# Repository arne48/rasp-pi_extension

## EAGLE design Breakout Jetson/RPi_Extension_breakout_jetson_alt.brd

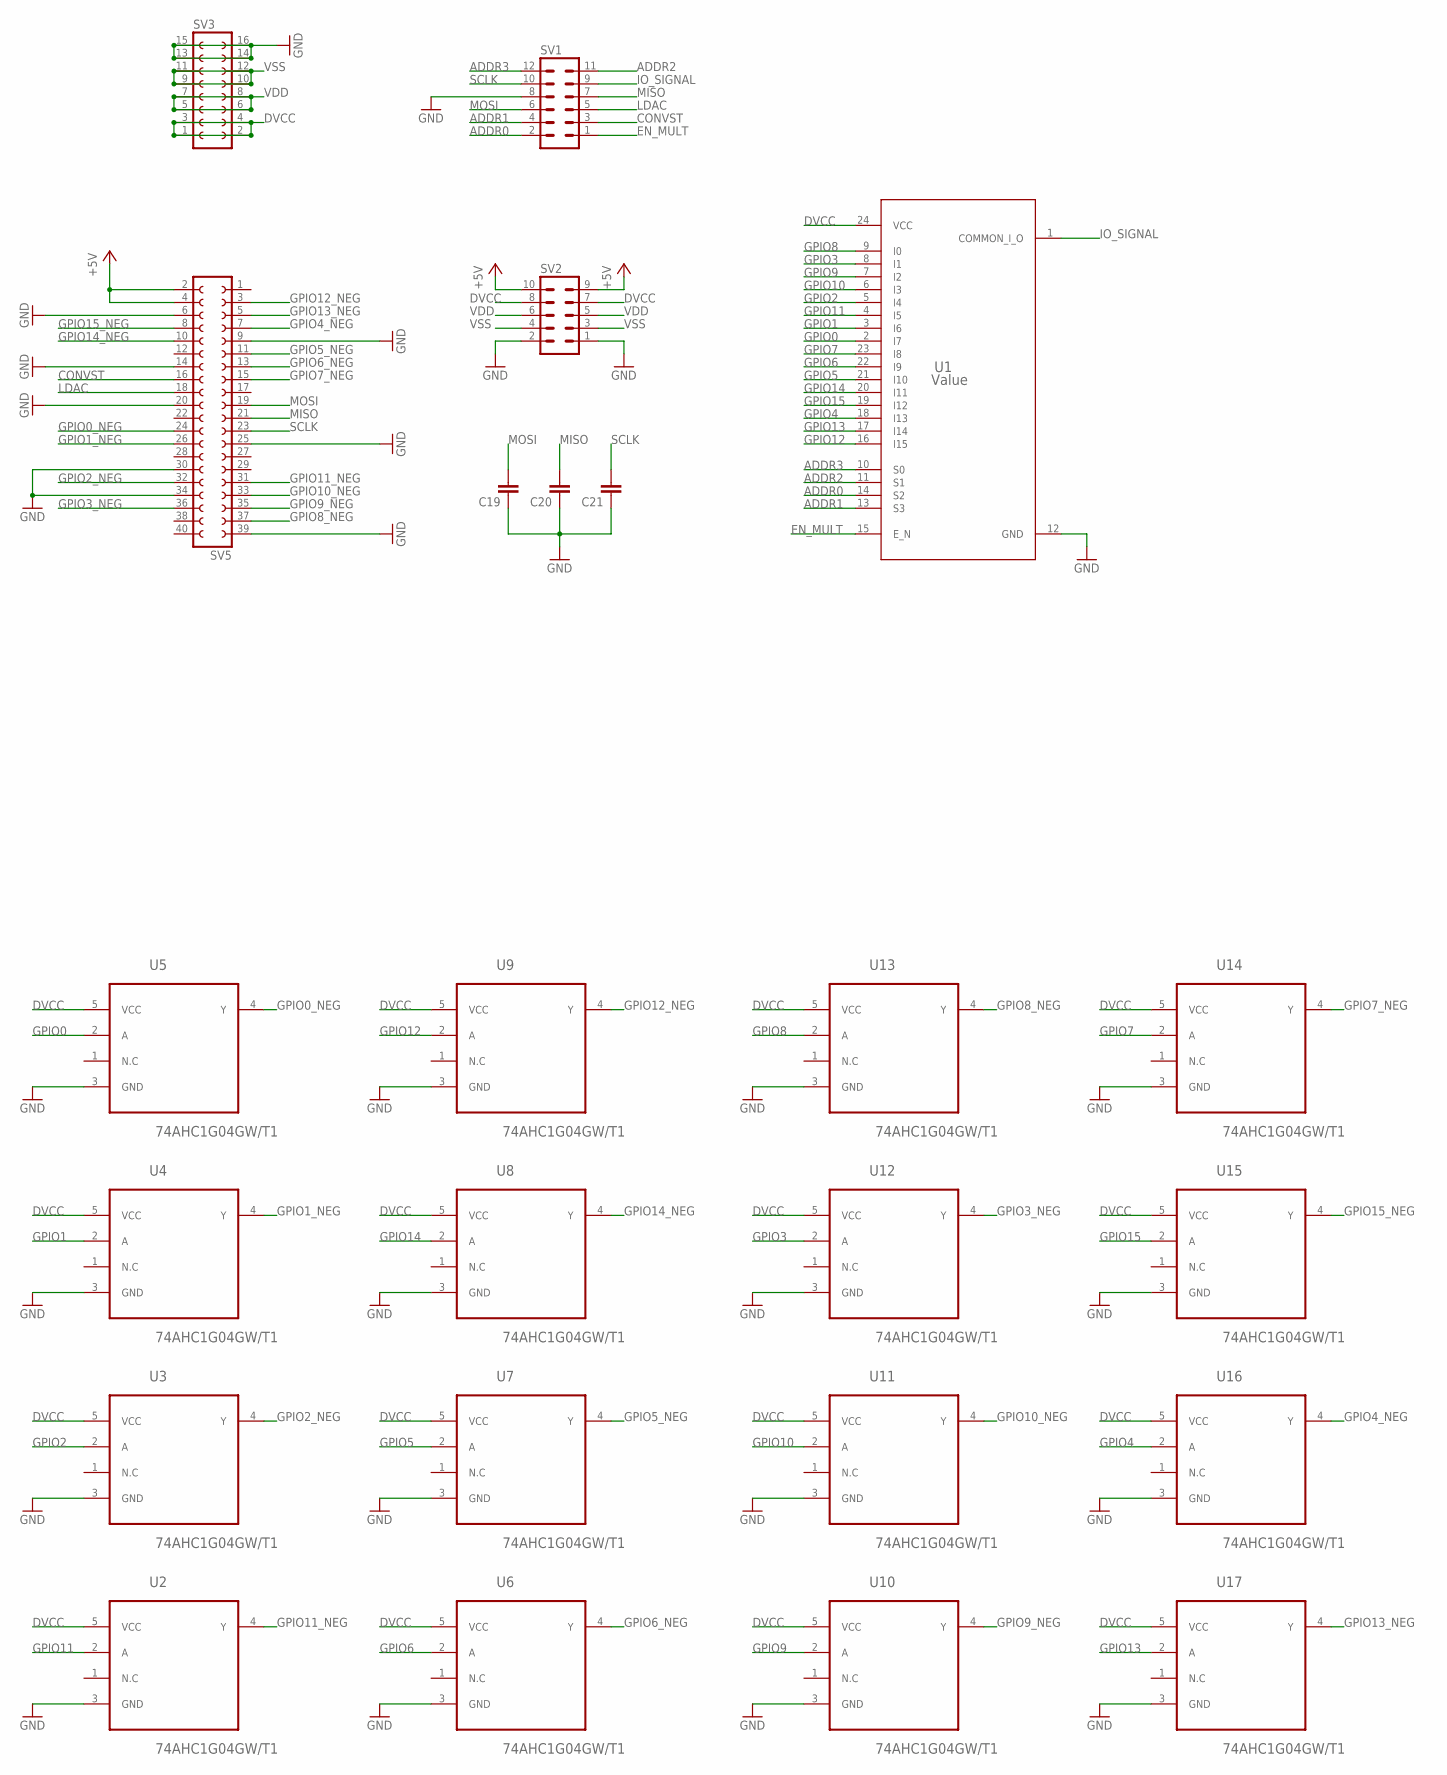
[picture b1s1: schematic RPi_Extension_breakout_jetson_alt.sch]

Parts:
C19, C20, C21: C-EUC0603; C0603
SV1: MA06-2
SV2: MA05-2
SV3: FE08-2
SV5: FE20-2
U1: Value; DB0024A_N
U2, U3, U4, U5, U6, U7, U8, U9, U10, U11, U12, U13, U14, U15, U16, U17: 74AHC1G04GW/T1; SOT65P210X110-5N

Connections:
+5V: SV2.9, SV2.10, SV5.2, SV5.4
ADDR0: SV1.2, U1.14 (S2)
ADDR1: SV1.4, U1.13 (S3)
ADDR2: SV1.11, U1.11 (S1)
ADDR3: SV1.12, U1.10 (S0)
CONVST: SV1.3, SV5.16
DVCC: SV2.7, SV2.8, SV3.1, SV3.2, SV3.3, SV3.4, U1.24 (VCC), U2.5 (VCC), U3.5 (VCC), U4.5 (VCC), U5.5 (VCC), U6.5 (VCC), U7.5 (VCC), U8.5 (VCC), U9.5 (VCC), U10.5 (VCC), U11.5 (VCC), U12.5 (VCC), U13.5 (VCC), U14.5 (VCC), U15.5 (VCC), U16.5 (VCC), U17.5 (VCC)
EN_MULT: SV1.1, U1.15 (E_N)
GND: C19.1, C20.1, C21.1, SV1.8, SV2.1, SV2.2, SV3.13, SV3.14, SV3.15, SV3.16, SV5.6, SV5.9, SV5.14, SV5.20, SV5.25, SV5.30, SV5.34, SV5.39, U1.12 (GND), U2.3 (GND), U3.3 (GND), U4.3 (GND), U5.3 (GND), U6.3 (GND), U7.3 (GND), U8.3 (GND), U9.3 (GND), U10.3 (GND), U11.3 (GND), U12.3 (GND), U13.3 (GND), U14.3 (GND), U15.3 (GND), U16.3 (GND), U17.3 (GND)
GPIO0: U1.2 (I7), U5.2 (A)
GPIO0_NEG: SV5.24, U5.4 (Y)
GPIO1: U1.3 (I6), U4.2 (A)
GPIO1_NEG: SV5.26, U4.4 (Y)
GPIO2: U1.5 (I4), U3.2 (A)
GPIO2_NEG: SV5.32, U3.4 (Y)
GPIO3: U1.8 (I1), U12.2 (A)
GPIO3_NEG: SV5.36, U12.4 (Y)
GPIO4: U1.18 (I13), U16.2 (A)
GPIO4_NEG: SV5.7, U16.4 (Y)
GPIO5: U1.21 (I10), U7.2 (A)
GPIO5_NEG: SV5.11, U7.4 (Y)
GPIO6: U1.22 (I9), U6.2 (A)
GPIO6_NEG: SV5.13, U6.4 (Y)
GPIO7: U1.23 (I8), U14.2 (A)
GPIO7_NEG: SV5.15, U14.4 (Y)
GPIO8: U1.9 (I0), U13.2 (A)
GPIO8_NEG: SV5.37, U13.4 (Y)
GPIO9: U1.7 (I2), U10.2 (A)
GPIO9_NEG: SV5.35, U10.4 (Y)
GPIO10: U1.6 (I3), U11.2 (A)
GPIO10_NEG: SV5.33, U11.4 (Y)
GPIO11: U1.4 (I5), U2.2 (A)
GPIO11_NEG: SV5.31, U2.4 (Y)
GPIO12: U1.16 (I15), U9.2 (A)
GPIO12_NEG: SV5.3, U9.4 (Y)
GPIO13: U1.17 (I14), U17.2 (A)
GPIO13_NEG: SV5.5, U17.4 (Y)
GPIO14: U1.20 (I11), U8.2 (A)
GPIO14_NEG: SV5.10, U8.4 (Y)
GPIO15: U1.19 (I12), U15.2 (A)
GPIO15_NEG: SV5.8, U15.4 (Y)
IO_SIGNAL: SV1.9, U1.1 (COMMON_I_O)
LDAC: SV1.5, SV5.18
MISO: C20.2, SV1.7, SV5.21
MOSI: C19.2, SV1.6, SV5.19
SCLK: C21.2, SV1.10, SV5.23
VDD: SV2.5, SV2.6, SV3.5, SV3.6, SV3.7, SV3.8
VSS: SV2.3, SV2.4, SV3.9, SV3.10, SV3.11, SV3.12

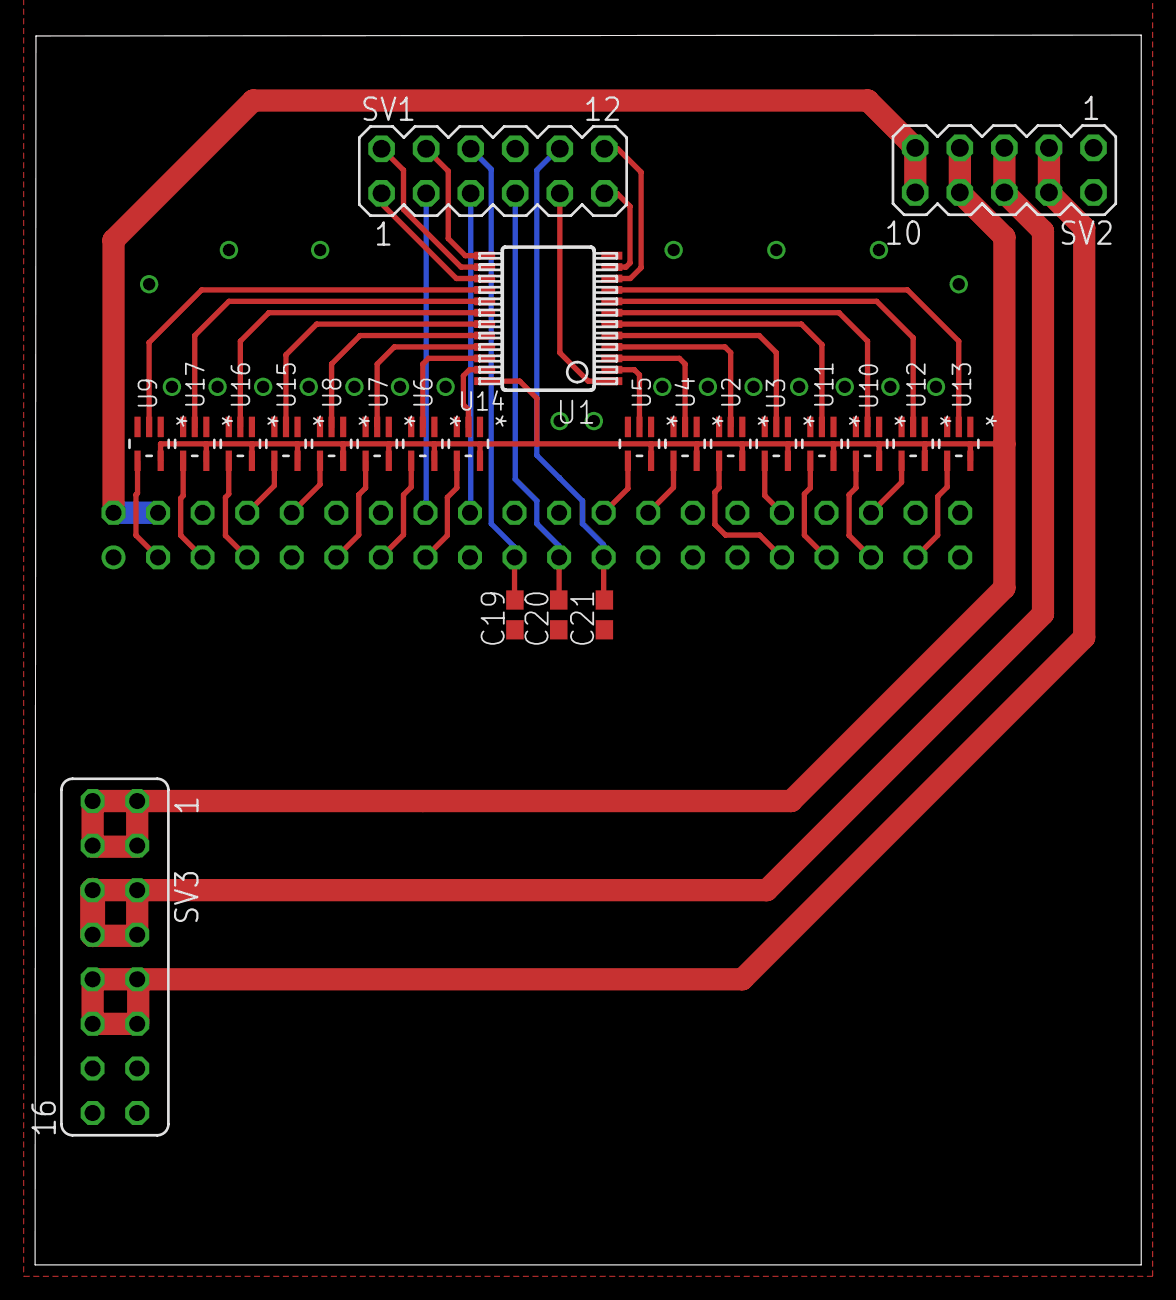
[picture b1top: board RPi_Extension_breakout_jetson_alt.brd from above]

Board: 2 copper layers, 63.0 x 70.1 mm, 24 parts (1 on the bottom side), 48 nets.

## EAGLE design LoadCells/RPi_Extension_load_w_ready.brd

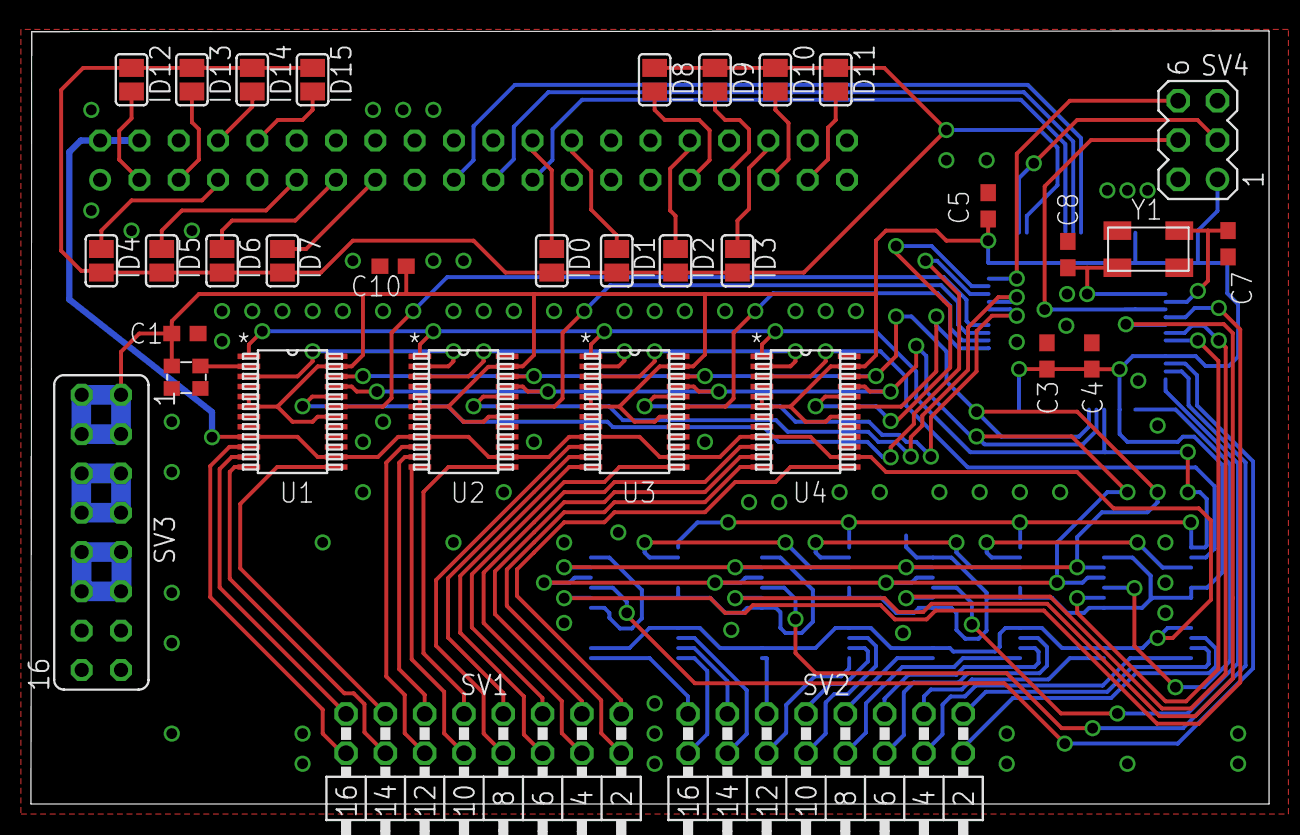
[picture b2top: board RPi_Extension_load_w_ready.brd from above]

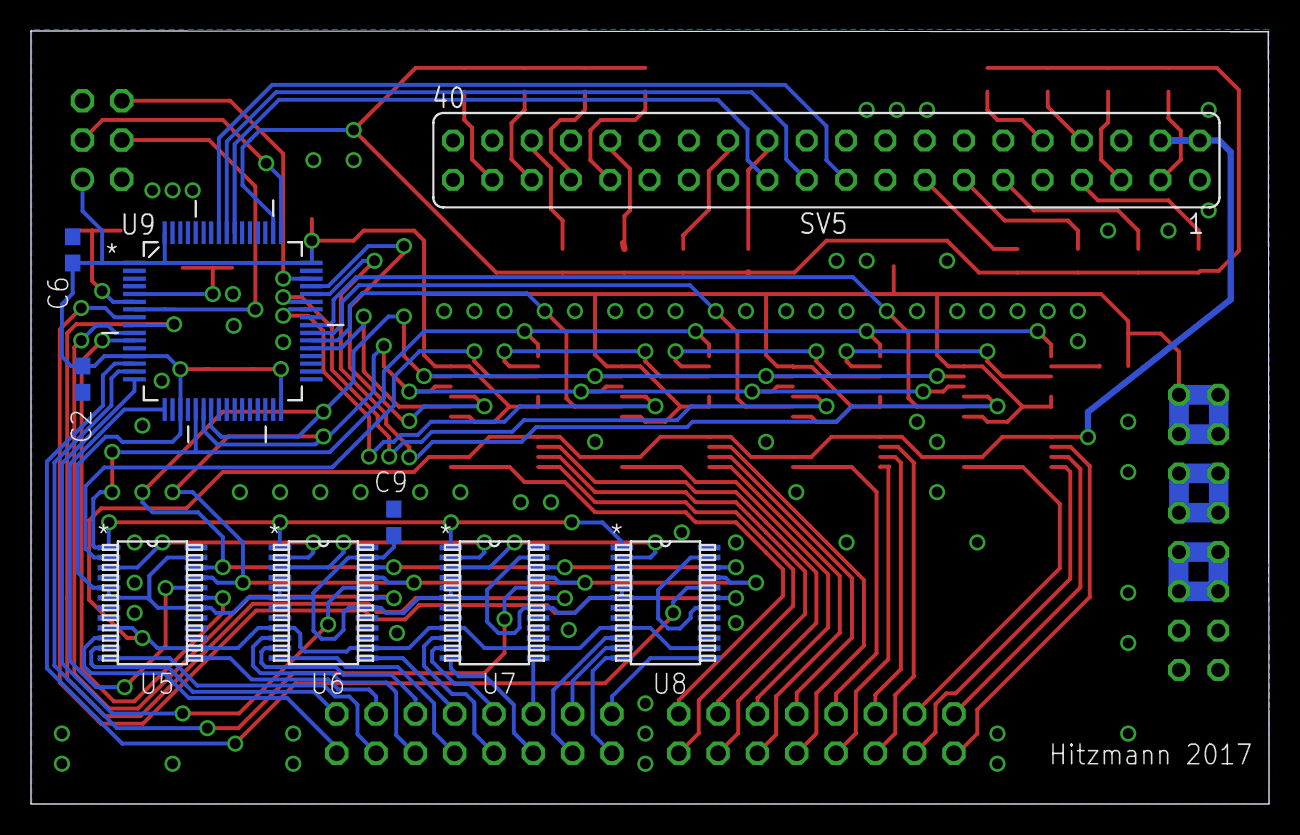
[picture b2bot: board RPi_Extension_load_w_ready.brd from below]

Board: 2 copper layers, 80.0 x 50.0 mm, 42 parts (9 on the bottom side), 89 nets.

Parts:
C1, C2, C3, C4, C5, C6, C9, C10: 100nF; C0603
C7, C8: 33pf; C0603
ID0, ID1, ID2, ID3, ID4, ID5, ID6, ID7, ID8, ID9, ID10, ID11, ID12, ID13, ID14, ID15: SJ
SV1, SV2: MA08-2W
SV3: FE08-2
SV4: MA03-2
SV5: FE20-2
U1, U2, U3, U4, U5, U6, U7, U8: AD7730BRUZ; RU_24
U9: STM32F103RCT6; QFP50P1200X1200X160-64N
Y1: ABM3B
Y2: KC2520B-C1

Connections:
+5V: SV5.2, SV5.4, U1.9, U1.14, U2.9, U2.14, U3.9, U3.14, U4.9, U4.14, U5.9, U5.14, U6.9, U6.14, U7.9, U7.14, U8.9, U8.14
DVCC: C1.2, C2.2, C3.1, C4.1, C5.1, C6.1, C9.1, C10.1, SV3.1, SV3.2, SV3.3, SV3.4, SV4.1, U1.5, U1.6, U1.18, U1.23, U2.5, U2.6, U2.18, U2.23, U3.5, U3.6, U3.18, U3.23, U4.5, U4.6, U4.18, U4.23, U5.5, U5.6, U5.18, U5.23, U6.5, U6.6, U6.18, U6.23, U7.5, U7.6, U7.18, U7.23, U8.5, U8.6, U8.18, U8.23, U9.1, U9.13, U9.19, U9.32, U9.48, U9.64, Y2.4
GND: C1.1, C2.1, C3.2, C4.2, C5.2, C6.2, C7.2, C8.2, C9.2, C10.2, SV3.13, SV3.14, SV3.15, SV3.16, SV4.2, SV4.5, SV5.6, SV5.9, SV5.14, SV5.20, SV5.25, SV5.30, SV5.34, SV5.39, U1.4, U1.8, U1.15, U1.24, U2.4, U2.8, U2.15, U2.24, U3.4, U3.8, U3.15, U3.24, U4.4, U4.8, U4.15, U4.24, U5.4, U5.8, U5.15, U5.24, U6.4, U6.8, U6.15, U6.24, U7.4, U7.8, U7.15, U7.24, U8.4, U8.8, U8.15, U8.24, U9.12, U9.18, U9.31, U9.47, U9.63, Y1.2, Y1.4, Y2.2
MCLK: U1.2, Y2.3
MISO: SV5.21, U9.56
MOSI: SV5.19, U9.57
unnamed: ID11.1, SV5.37
unnamed: C8.1, U9.5, Y1.1
unnamed: C7.1, U9.6, Y1.3
unnamed: ID10.1, SV5.35
unnamed: ID9.1, SV5.33
unnamed: ID8.1, SV5.31
unnamed: ID14.1, SV5.8
unnamed: ID15.1, SV5.10
unnamed: ID12.1, SV5.3
unnamed: ID13.1, SV5.5
unnamed: ID3.1, SV5.36
unnamed: ID4.1, SV5.7
unnamed: ID2.1, SV5.32
unnamed: ID1.1, SV5.26
unnamed: ID0.1, SV5.24
unnamed: ID5.1, SV5.11
unnamed: ID6.1, SV5.13
unnamed: ID7.1, SV5.15
NRST: SV4.4, U9.7
RDY1: U1.20, U9.44
RDY2: U2.20, U9.43
RDY3: U3.20, U9.42
RDY4: U4.20, U9.45
RDY5: U5.20, U9.17
RDY6: U6.20, U9.16
RDY7: U7.20, U9.15
RDY8: U8.20, U9.14
SCLK: SV5.23, U9.55
SPI1_MISO: U1.21, U2.21, U3.21, U4.21, U5.21, U6.21, U7.21, U8.21, U9.22
SPI1_MOSI: U1.22, U2.22, U3.22, U4.22, U5.22, U6.22, U7.22, U8.22, U9.23
SPI1_SCK: U1.1, U2.1, U3.1, U4.1, U5.1, U6.1, U7.1, U8.1, U9.21
SS1: U1.19, U9.40
SS2: U2.19, U9.39
SS3: U3.19, U9.38
SS4: U4.19, U9.37
SS5: U5.19, U9.11
SS6: U6.19, U9.10
SS7: U7.19, U9.9
SS8: U8.19, U9.8
SS_STACK: ID0.2, ID1.2, ID2.2, ID3.2, ID4.2, ID5.2, ID6.2, ID7.2, ID8.2, ID9.2, ID10.2, ID11.2, ID12.2, ID13.2, ID14.2, ID15.2, U9.50
SWDCLK: SV4.3, U9.49
SWDIO: SV4.6, U9.46
U1_AIN1_+: SV1.16, U1.10
U1_AIN1_-: SV1.15, U1.11
U1_AIN2_+: SV1.14, U1.12
U1_AIN2_-: SV1.13, U1.13
U1_MCLK_OUT: U1.3, U2.2
U2_AIN1_+: SV1.12, U2.10
U2_AIN1_-: SV1.11, U2.11
U2_AIN2_+: SV1.10, U2.12
U2_AIN2_-: SV1.9, U2.13
U2_MCLK_OUT: U2.3, U3.2
U3_AIN1_+: SV1.8, U3.10
U3_AIN1_-: SV1.7, U3.11
U3_AIN2_+: SV1.6, U3.12
U3_AIN2_-: SV1.5, U3.13
U3_MCLK_OUT: U3.3, U4.2
U4_AIN1_+: SV1.4, U4.10
U4_AIN1_-: SV1.3, U4.11
U4_AIN2_+: SV1.2, U4.12
U4_AIN2_-: SV1.1, U4.13
U4_MCLK_OUT: U4.3, U5.2
U5_AIN1_+: SV2.2, U5.10
U5_AIN1_-: SV2.1, U5.11
U5_AIN2_+: SV2.4, U5.12
U5_AIN2_-: SV2.3, U5.13
U5_MCLK_OUT: U5.3, U6.2
U6_AIN1_+: SV2.6, U6.10
U6_AIN1_-: SV2.5, U6.11
U6_AIN2_+: SV2.8, U6.12
U6_AIN2_-: SV2.7, U6.13
U6_MCLK_OUT: U6.3, U7.2
U7_AIN1_+: SV2.10, U7.10
U7_AIN1_-: SV2.9, U7.11
U7_AIN2_+: SV2.12, U7.12
U7_AIN2_-: SV2.11, U7.13
U7_MCLK_OUT: U7.3, U8.2
U8_AIN1_+: SV2.14, U8.10
U8_AIN1_-: SV2.13, U8.11
U8_AIN2_+: SV2.16, U8.12
U8_AIN2_-: SV2.15, U8.13
VDD: SV3.5, SV3.6, SV3.7, SV3.8
VSS: SV3.9, SV3.10, SV3.11, SV3.12

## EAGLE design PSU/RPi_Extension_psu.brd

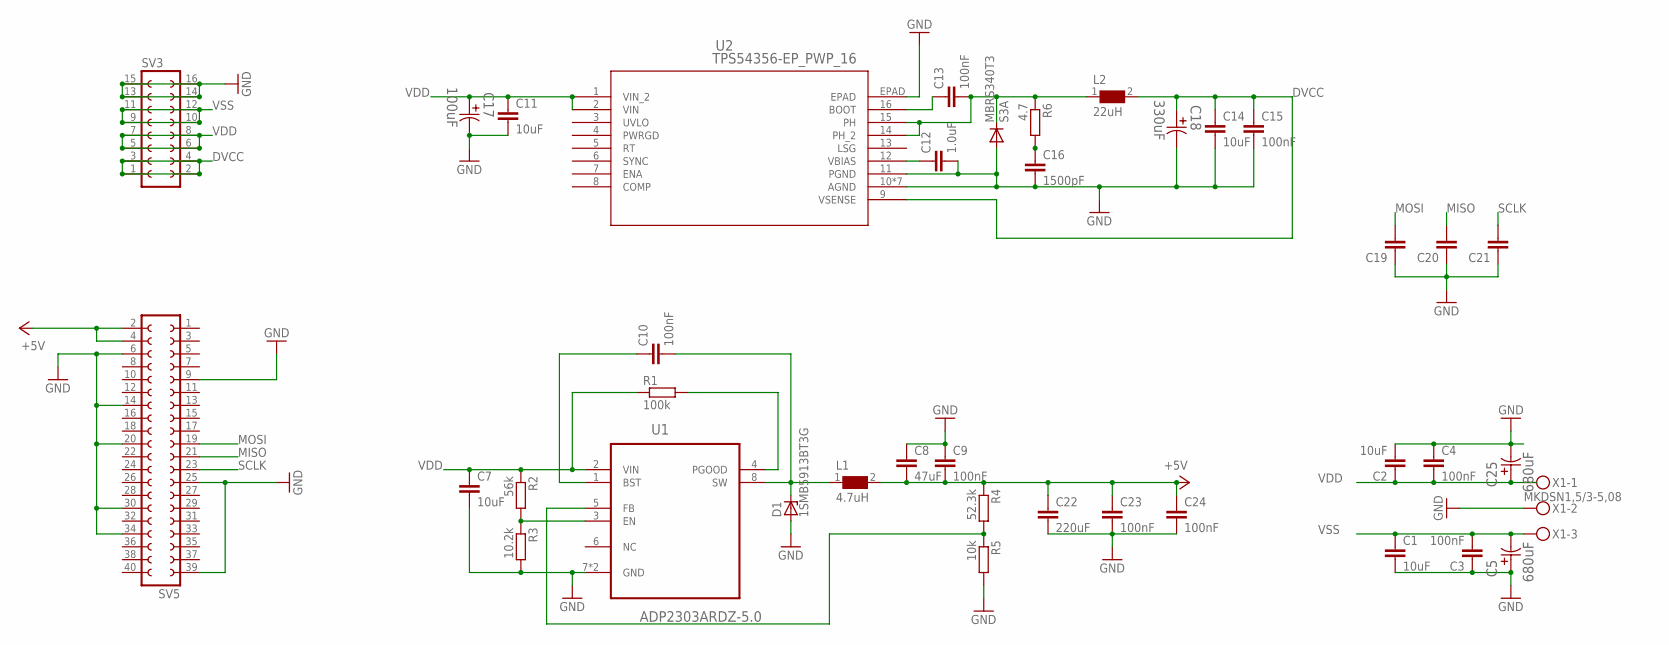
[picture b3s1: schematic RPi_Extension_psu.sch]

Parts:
C1, C2: 10uF; C1206
C3, C4, C9, C10, C13, C15, C23, C24: 100nF; C0603
C5, C25: 680uF; CAPAE830X1050N
C7, C11, C14: 10uF; C0603
C8: 47uF; C0603
C12: 1.0uF; C0603
C16: 1500pF; C0603
C17: 100uF; CAPAE660X800N
C18: 330uF; CAPAE1030X1050N
C19, C20, C21: C-EUC0603; C0603
C22: 220uF; C1206
D1: 1SMB5913BT3G; DO214AA
L1: 4.7uH; WE-PD_1030/1050
L2: 22uH; WE-PD_1260/1245/1280/1210
MBRS340T3: S3A; DO214AB
R1: 100k; R0603
R2: 56k; R0603
R3: 10.2k; R0603
R4: 52.3k; R0603
R5: 10k; R0603
R6: 4.7; R0603
SV3: FE08-2
SV5: FE20-2
U1: ADP2303ARDZ-5.0; SOIC127P600X175-9N
U2: TPS54356-EP_PWP_16; PWP16_2P31X2P46
X1: MKDSN1,5/3-5,08

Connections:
+5V: C8.2, C9.2, C22.1, C23.1, C24.1, L1.2, R4.1, SV5.2, SV5.4
DVCC: C14.1, C15.1, C18.1, L2.2, SV3.1, SV3.2, SV3.3, SV3.4, U2.9 (VSENSE)
GND: C1.2, C2.2, C3.1, C4.1, C5.1, C7.2, C8.1, C9.1, C11.2, C12.2, C14.2, C15.2, C16.2, C17.2, C18.2, C19.1, C20.1, C21.1, C22.2, C23.2, C24.2, C25.2, D1.A, MBRS340T3.A, R3.2, R5.2, SV3.13, SV3.14, SV3.15, SV3.16, SV5.6, SV5.9, SV5.14, SV5.20, SV5.25, SV5.30, SV5.34, SV5.39, U1.7 (GND), U1.9 (GND), U2.10 (AGND), U2.11 (PGND), U2.EPAD, U2.V (AGND), U2.V_1 (AGND), U2.V_2 (AGND), U2.V_3 (AGND), U2.V_4 (AGND), U2.V_5 (AGND), X1.2
MISO: C20.2, SV5.21
MOSI: C19.2, SV5.19
unnamed: R1.2, U1.4 (PGOOD)
unnamed: C10.1, U1.1 (BST)
unnamed: R2.2, R3.1, U1.3 (EN)
unnamed: C10.2, D1.C, L1.1, U1.8 (SW)
unnamed: R4.2, R5.1, U1.5 (FB)
unnamed: C13.1, U2.16 (BOOT)
unnamed: C12.1, U2.12 (VBIAS)
unnamed: C16.1, R6.2
PWRGD: U2.4 (PWRGD)
SCLK: C21.2, SV5.23
VDD: C2.1, C4.2, C7.1, C11.1, C17.1, C25.1, R1.1, R2.1, SV3.5, SV3.6, SV3.7, SV3.8, U1.2 (VIN), U2.1 (VIN_2), U2.2 (VIN), X1.1
VOUT: C13.2, L2.1, MBRS340T3.C, R6.1, U2.14 (PH_2), U2.15 (PH)
VSS: C1.1, C3.2, C5.2, SV3.9, SV3.10, SV3.11, SV3.12, X1.3

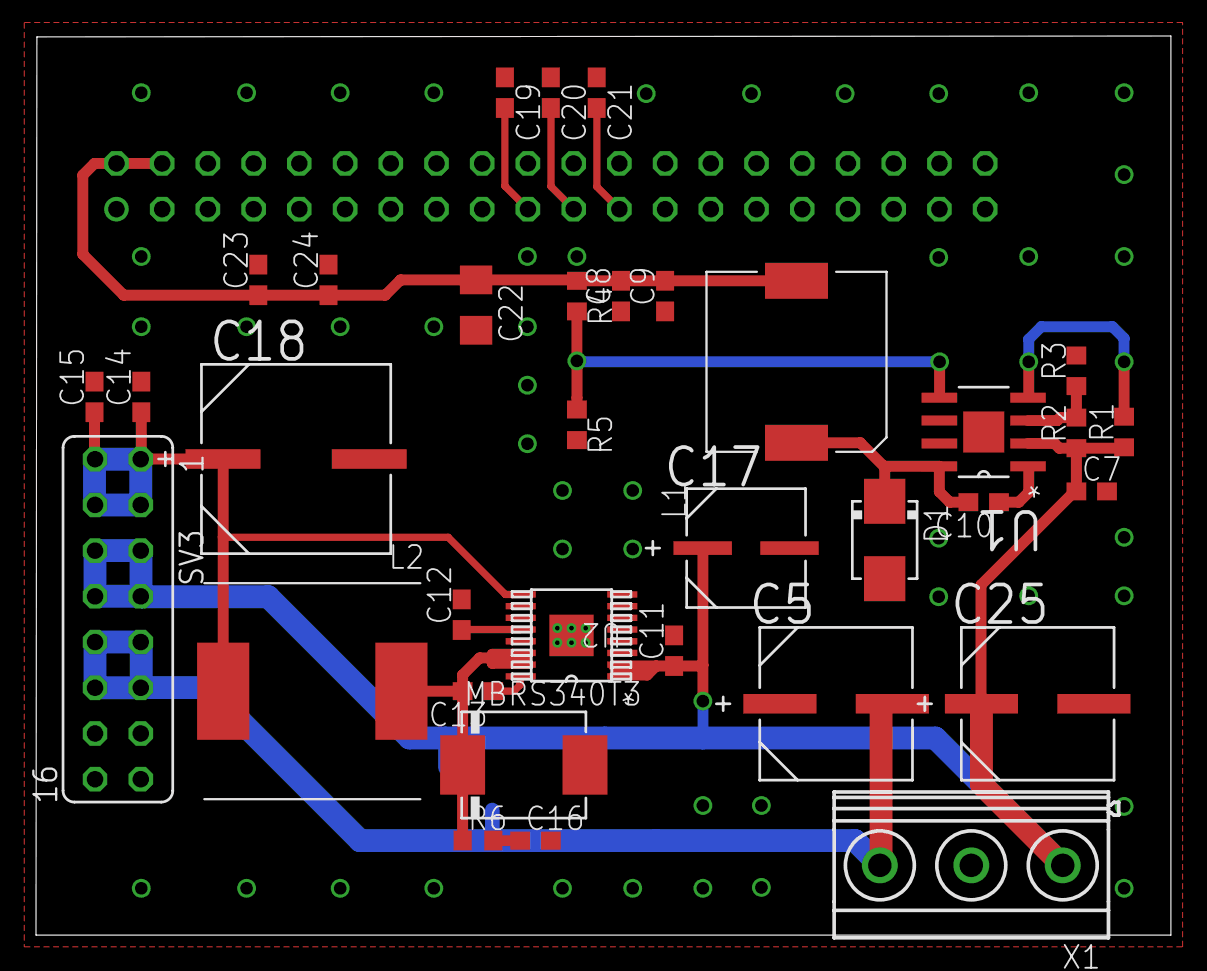
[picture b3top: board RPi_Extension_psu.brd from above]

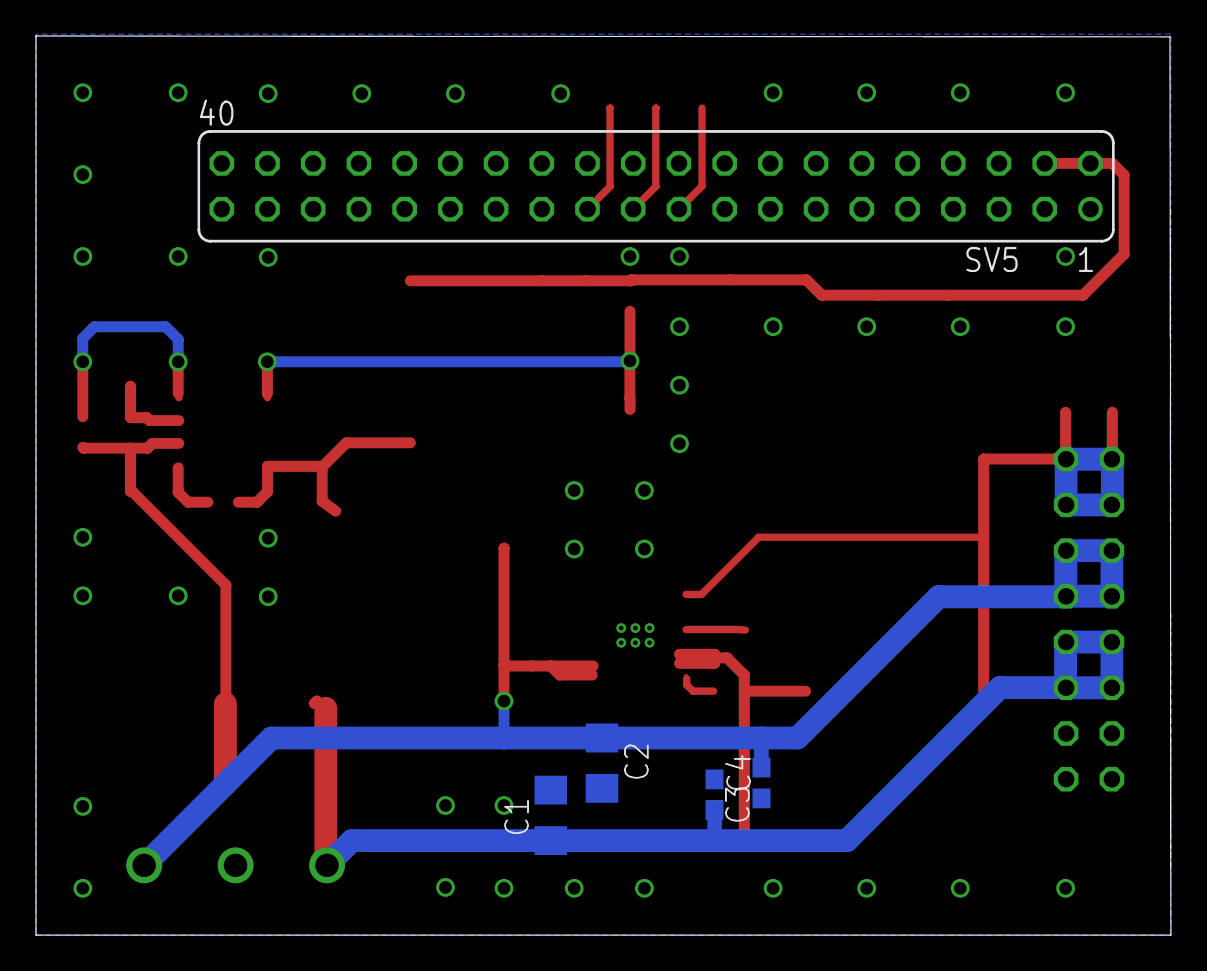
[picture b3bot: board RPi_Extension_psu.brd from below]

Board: 2 copper layers, 63.0 x 50.0 mm, 39 parts (5 on the bottom side), 17 nets.
